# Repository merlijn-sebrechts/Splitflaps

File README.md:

Splitflaps
==========
This project contains all the technical information I have from the SPLITFLAPS project.

I started this project as part of my studies, an continued to work on it after my studies. However, due to lack of time, I stopped working on it.

related:
http://splitflaps.wordpress.com/
http://www.0x20.be/Project_Flappers
https://www.youtube.com/user/Galgaleshe/videos

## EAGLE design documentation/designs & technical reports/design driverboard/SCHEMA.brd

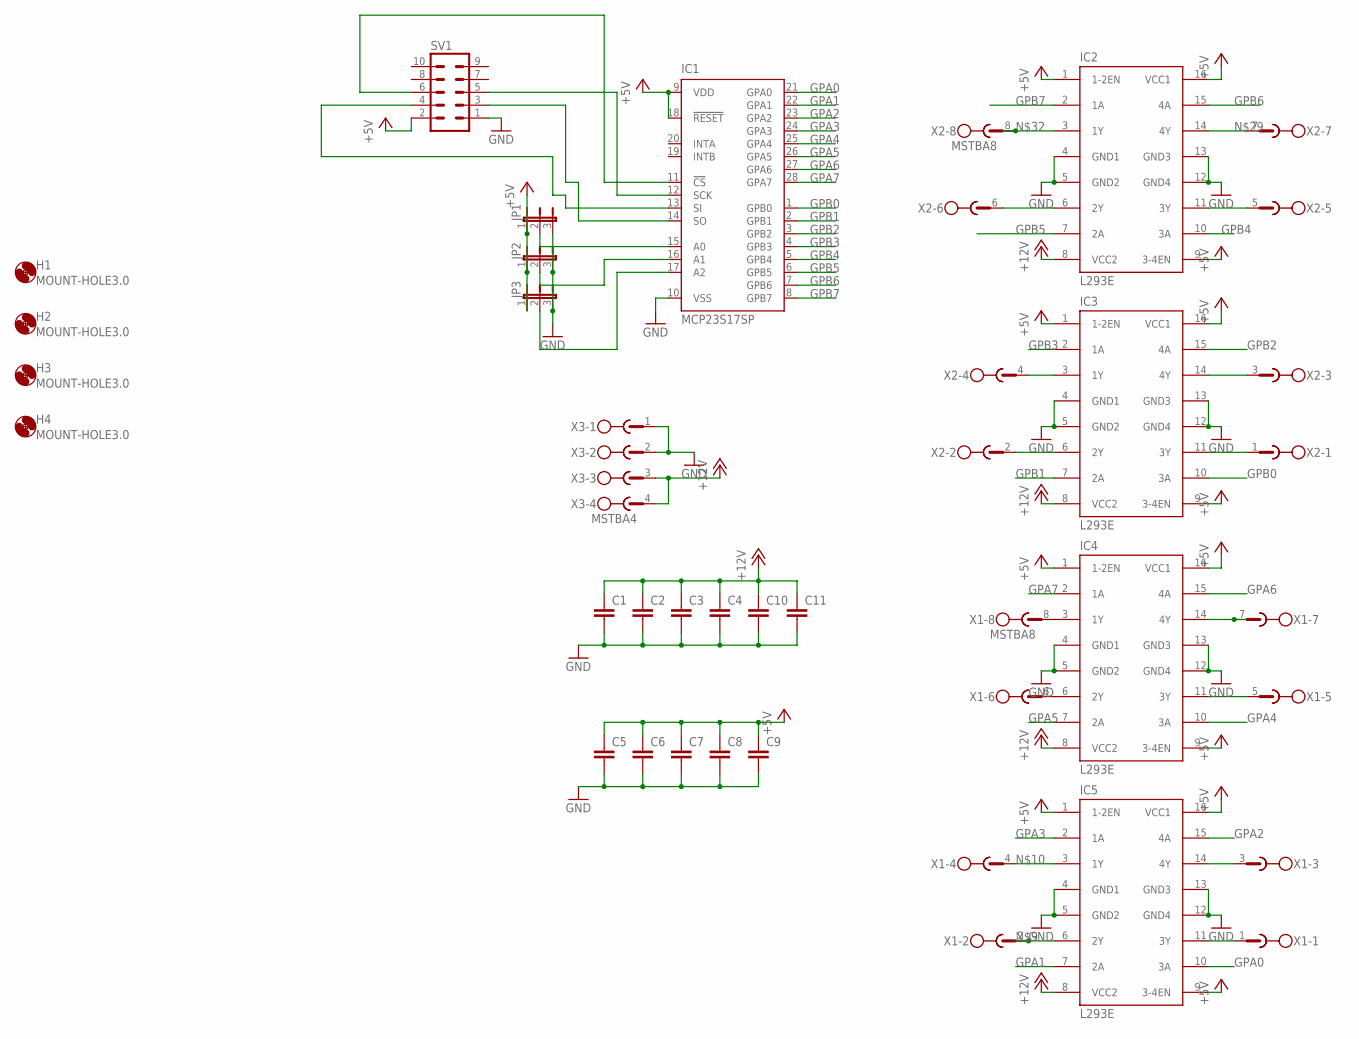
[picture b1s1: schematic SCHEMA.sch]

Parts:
C1, C2, C3, C4, C5, C6, C7, C8, C9, C10, C11: C-EU025-025X050; C025-025X050
H1, H2, H3, H4: MOUNT-HOLE3.0; 3,0
IC1: MCP23S17SP; DIL28-3
IC2, IC3, IC4, IC5: L293E; DIL16
JP1, JP2, JP3: JP2E; JP2
SV1: ML10
X1, X2: MSTBA8
X3: MSTBA4

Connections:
+5V: C5.1, C6.1, C7.1, C8.1, C9.1, IC1.9 (VDD), IC1.18 (!RESET), IC2.1 (1-2EN), IC2.9 (3-4EN), IC2.16 (VCC1), IC3.1 (1-2EN), IC3.9 (3-4EN), IC3.16 (VCC1), IC4.1 (1-2EN), IC4.9 (3-4EN), IC4.16 (VCC1), IC5.1 (1-2EN), IC5.9 (3-4EN), IC5.16 (VCC1), JP1.1, JP2.1, JP3.1, SV1.2
+12V: C1.1, C2.1, C3.1, C4.1, C10.1, C11.1, IC2.8 (VCC2), IC3.8 (VCC2), IC4.8 (VCC2), IC5.8 (VCC2), X3.3, X3.4
GND: C1.2, C2.2, C3.2, C4.2, C5.2, C6.2, C7.2, C8.2, C9.2, C10.2, C11.2, IC1.10 (VSS), IC2.4 (GND1), IC2.5 (GND2), IC2.12 (GND4), IC2.13 (GND3), IC3.4 (GND1), IC3.5 (GND2), IC3.12 (GND4), IC3.13 (GND3), IC4.4 (GND1), IC4.5 (GND2), IC4.12 (GND4), IC4.13 (GND3), IC5.4 (GND1), IC5.5 (GND2), IC5.12 (GND4), IC5.13 (GND3), JP1.3, JP2.3, JP3.3, SV1.1, X3.1, X3.2
GPA0: IC1.21 (GPA0), IC5.10 (3A)
GPA1: IC1.22 (GPA1), IC5.7 (2A)
GPA2: IC1.23 (GPA2), IC5.15 (4A)
GPA3: IC1.24 (GPA3), IC5.2 (1A)
GPA4: IC1.25 (GPA4), IC4.10 (3A)
GPA5: IC1.26 (GPA5), IC4.7 (2A)
GPA6: IC1.27 (GPA6), IC4.15 (4A)
GPA7: IC1.28 (GPA7), IC4.2 (1A)
GPB0: IC1.1 (GPB0), IC3.10 (3A)
GPB1: IC1.2 (GPB1), IC3.7 (2A)
GPB2: IC1.3 (GPB2), IC3.15 (4A)
GPB3: IC1.4 (GPB3), IC3.2 (1A)
GPB4: IC1.5 (GPB4), IC2.10 (3A)
GPB5: IC1.6 (GPB5), IC2.7 (2A)
GPB6: IC1.7 (GPB6), IC2.15 (4A)
GPB7: IC1.8 (GPB7), IC2.2 (1A)
unnamed: IC4.6 (2Y), X1.6
unnamed: IC4.3 (1Y), X1.8
unnamed: IC1.14 (SO), SV1.3
unnamed: IC1.15 (A0), JP1.2
unnamed: IC1.16 (A1), JP2.2
unnamed: IC1.17 (A2), JP3.2
unnamed: IC1.13 (SI), SV1.4
unnamed: IC1.12 (SCK), SV1.5
unnamed: IC5.6 (2Y), X1.2
unnamed: IC5.3 (1Y), X1.4
unnamed: IC1.11 (!CS), SV1.6
unnamed: IC5.14 (4Y), X1.3
unnamed: IC5.11 (3Y), X1.1
unnamed: IC4.14 (4Y), X1.7
unnamed: IC4.11 (3Y), X1.5
unnamed: IC3.14 (4Y), X2.3
unnamed: IC3.11 (3Y), X2.1
unnamed: IC3.3 (1Y), X2.4
unnamed: IC3.6 (2Y), X2.2
unnamed: IC2.14 (4Y), X2.7
unnamed: IC2.11 (3Y), X2.5
unnamed: IC2.6 (2Y), X2.6
unnamed: IC2.3 (1Y), X2.8

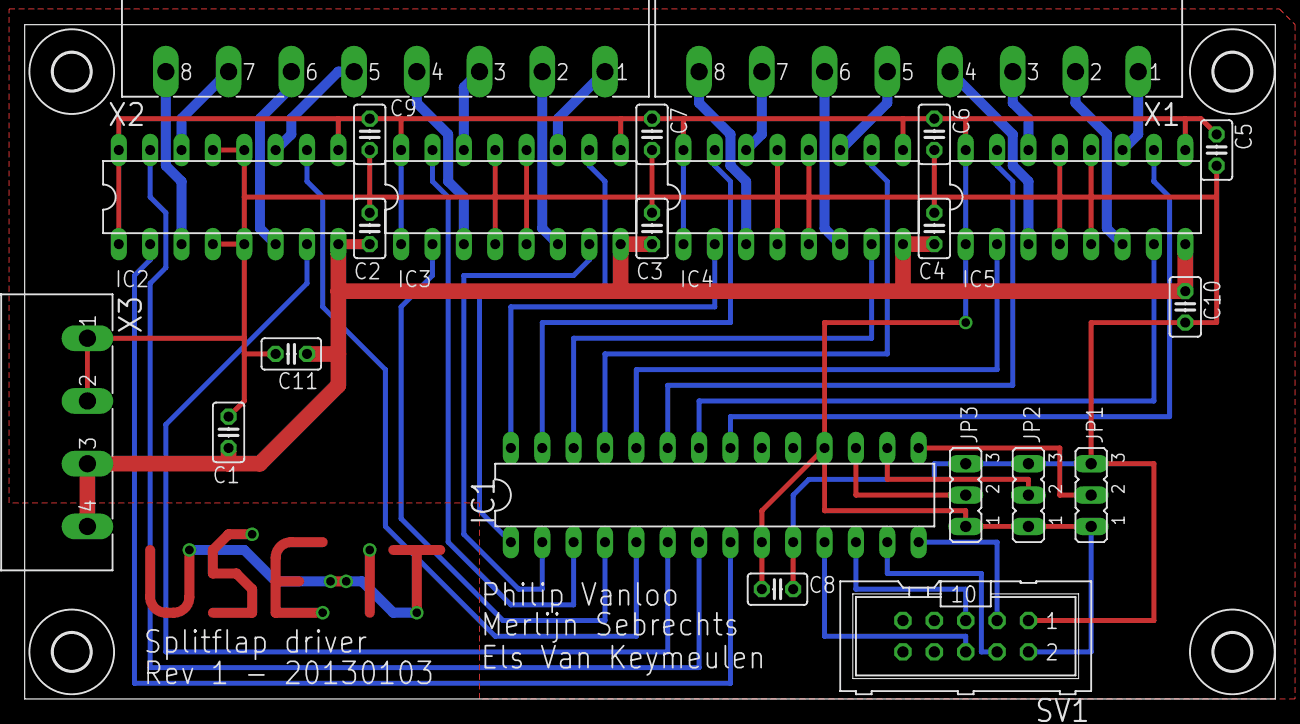
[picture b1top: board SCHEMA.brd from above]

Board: 2 copper layers, 101.3 x 54.6 mm, 27 parts (0 on the bottom side), 42 nets.

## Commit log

2013-02-05 code with default address
2013-02-05 code with default address and real address
2013-02-15 first
2013-02-17 working code for chip
2013-02-17 working with 2 addresses
2013-02-18 working commit
2013-10-25 changed directory structure, added drawings
2013-10-25 added files from old project
2013-10-27 added some pictures
2013-11-29 added more information and schemes
2013-11-29 Media => media
2013-11-29 renamed, because the name was confusing
2013-11-29 added design driverboard
